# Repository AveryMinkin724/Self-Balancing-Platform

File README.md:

# Self-Balancing-Platform
Contains all sprints as part of development of the self balancing platform project

# ICD

# Settings
Uart.c
- choose between Bluetooth or USB mode for UART comms in line 7

imu.c
- choose whether to use hardcoded bias values or run new calibration in line 9

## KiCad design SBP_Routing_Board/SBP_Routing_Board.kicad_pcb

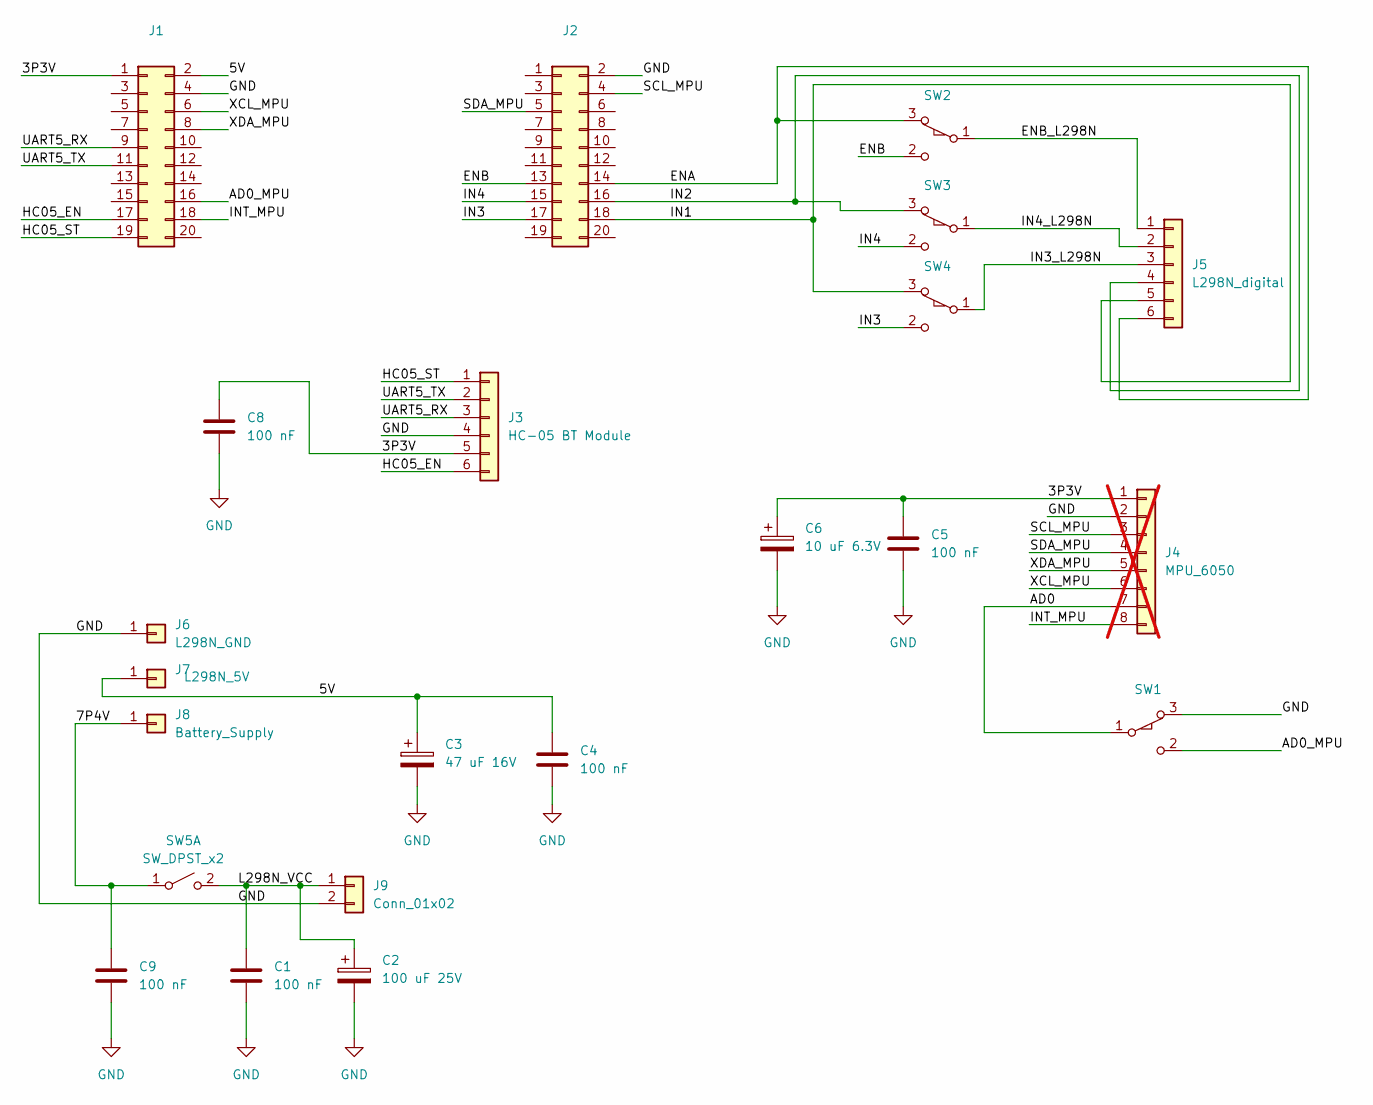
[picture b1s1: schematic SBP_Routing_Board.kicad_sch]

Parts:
C1, C4, C5, C8, C9: 100 nF; C_0603_1608Metric_Pad1.08x0.95mm_HandSolder
C2: 100 uF 25V; CP_Elec_6.3x5.4
C3: 47 uF 16V; CP_Elec_6.3x5.7
C6: 10 uF 6.3V; CP_Elec_6.3x5.7
J1, J2: Conn_02x10_Odd_Even; PinHeader_2x10_P2.54mm_Vertical
J3: HC-05 BT Module; PinHeader_1x06_P2.54mm_Vertical
J4: MPU_6050; PinHeader_1x08_P2.54mm_Vertical; not fitted
J5: L298N_digital; PinHeader_1x06_P2.54mm_Vertical
J6: L298N_GND; TestPoint_THTPad_D2.5mm_Drill1.2mm
J7: L298N_5V; TestPoint_THTPad_D2.5mm_Drill1.2mm
J8: Battery_Supply; TestPoint_THTPad_D2.5mm_Drill1.2mm
J9: Conn_01x02; PinHeader_1x02_P2.54mm_Vertical
SW1, SW2, SW3, SW4: SW_SPDT_XKB_DMx-xxxx-1; SW_SPDT_CK_JS102011SAQN
SW5: SW_DPST_x2; SW_DIP_SPSTx01_Slide_Copal_CHS-01A_W5.08mm_P1.27mm_JPin

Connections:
/3P3V: C5.1, C6.1, C8.1, J1.1 (3.3V), J3.5 (VCC), J4.1
/5V: C3.1, C4.1, J1.2 (VBUS), J7.1
/7P4V: C9.1, J8.1, SW5.1 (A)
/AD0: J4.7, SW1.1 (A)
/AD0_MPU: J1.16, SW1.2 (B)
/ENA: J2.14, J5.6 (EN), SW2.3 (C)
/ENB: J2.13, SW2.2 (B)
/ENB_L298N: J5.1 (STATE), SW2.1 (A)
/HC05_EN: J1.17 (PA6), J3.6 (EN)
/HC05_ST: J1.19 (PA7), J3.1 (STATE)
/IN1: J2.18, J5.5 (VCC), SW4.3 (C)
/IN2: J2.16, J5.4 (GND), SW3.3 (C)
/IN3: J2.17, SW4.2 (B)
/IN3_L298N: J5.3 (TXD), SW4.1 (A)
/IN4: J2.15, SW3.2 (B)
/IN4_L298N: J5.2 (RXD), SW3.1 (A)
/INT_MPU: J1.18, J4.8
/L298N_VCC: C1.1, C2.1, J9.1, SW5.2 (B)
/SCL_MPU: J2.4, J4.3
/SDA_MPU: J2.5, J4.4
/UART5_RX: J1.9 (PE4), J3.3 (TXD)
/UART5_TX: J1.11 (PE5), J3.2 (RXD)
/XCL_MPU: J1.6, J4.6
/XDA_MPU: J1.8, J4.5
GND: C1.2, C2.2, C3.2, C4.2, C5.2, C6.2, C8.2, C9.2, J1.4 (GND), J2.2, J3.4 (GND), J4.2, J6.1, J9.2, SW1.3 (C)

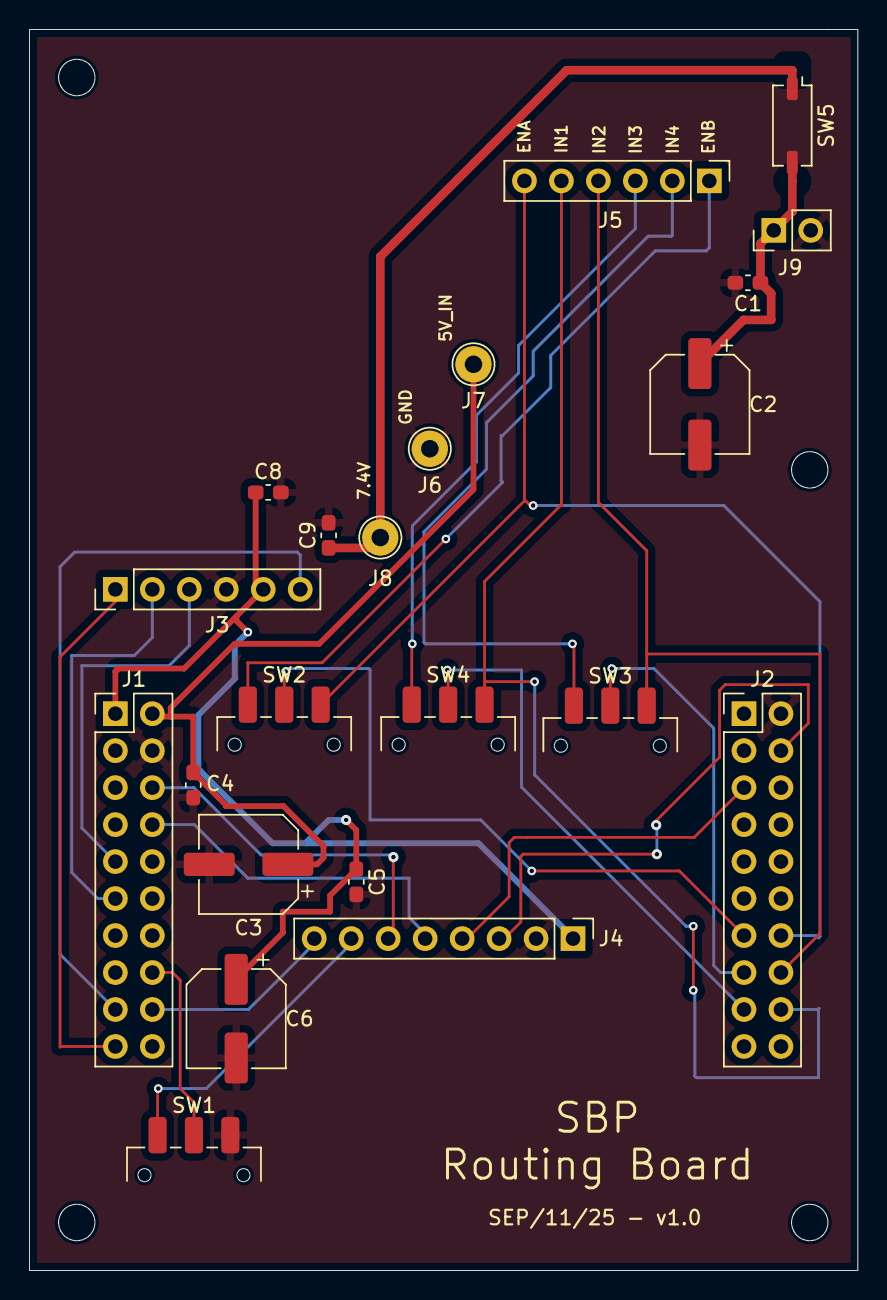
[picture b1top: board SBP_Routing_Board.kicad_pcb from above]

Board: 4 copper layers, 56.9 x 85.2 mm, 23 parts (0 on the bottom side), 25 nets.

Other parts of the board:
REF: MountingHole_2.5mm

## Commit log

2025-05-31 Initial Commit with Sprint 1 and shared libraries
2025-05-31 Add Sprint 1 folder as a normal directory (not a submodule)
2025-05-31 Re-add Sprint_1 folder as regular directory
2025-06-04 changed 3 task names and print to putty terminal in each task
2025-06-04 added UART Logger Task
2025-06-05 starting sprint 2
2025-06-12 added mmotor task which for now just prints to uart, and motor_init in bsp.c
2025-06-20 added sprint 3 IMU task which just reads MPU6050 ID: 0x68
2025-06-23 debugged reading values from MPU6050, can now read XYZ, UVW
2025-06-24 added imu calibration
2025-07-03 Added Complementary fliter
2025-07-11 Added PID control
2025-07-14 PID working with motor task
2025-07-28 Add Sprint 4 Bluetooth module folder
2025-07-28 WIP: local changes
2025-08-15 UART5_IRQHander working, can send uart messages to tivaC interrupt driven
2025-09-28 Routing Board and Chassis Files Added
2025-11-26 operating SBP with PID parameters somewhat tuned
2026-01-31 Adding sprint 5: deterministic timing & clamp on delta_output
